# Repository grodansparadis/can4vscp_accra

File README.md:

-----

# The CAN4VSCP Accra general counter module</h1>

This module is part of the [VSCP project](https://www.vscp.org).  It is free to use, modify and sell. The only thing we kindly ask is that improvements and extensions are contributed back to the project (at your will). This to make the project better for everyone. All design files is licensed under the [MIT license](https://en.wikipedia.org/wiki/MIT_License).

The module is documented [here](https://grodansparadis.github.io/can4vscp_accra/#/)

## Abstract

Accra is a general counter module that connects to a CAN4VSCP bus and can count pulses on four channels. The module can be attached to a standard DIN Rail or be mounted directly on a wall.

The module fully adopts to the CAN4VSCP specification and can be powered directly over the bus with a 9-28V DC power source. It has a rich register set for configuration and any information events defined. It also have a decision matrix for easy dynamic event handling.

VSCP CAN modules are designed to work on a VSCP4CAN bus which use ordinary RJ-45 connectors and is powered with 9-30V DC over the same cable. This means there is no need for a separate power cable. All that is needed is a CAT5 or better twisted pair cable. Bus length can be a maximum of 500 meters with drops of maximum 24 meters length (up to a total of 120 meters). As for all VSCP4CAN modules the communication speed is fixed at 125 kbps.

All VSCP modules contains information of there own setup, manual, hardware version, manufacturer etc. You just ask the module for the information you need and you will get it. When they are started up they have a default functionality that often is all that is needed to get a working setup. If the module have something to report it will send you an event and if it is setup to react on a certain type of event it will do it's work when you send event(s) to it. 

---

## Project files

### User manual
  * [User Manual](https://grodansparadis.github.io/can4vscp_accra/#)

### Schematic, PCB, 3D files etc
  * [Schematics reversion A](https://raw.githubusercontent.com/grodansparadis/can4vscp_accra/refs/heads/master/eagle/accra_sch_rev_A.png)
 * Hardware design files is made in [KiCad](https://kicad.org) and can be found in the `kicad` directory. Valid from reversion B of the hardware.
   * Gerber files for PCB production can be found in the `gerber` directory (in the `kicad` folder).
 * Eagle schema and board files for reversion A and B can be found in the `eagle` directory. They are no longer actively updated.

 ### Firmware

 The firmware is developed in [MPLAB X IDE](https://www.microchip.com/mplab/mplab-x-ide) using the [XC8 compiler](https://www.microchip.com/mplab/compilers).

  * Binary release files is available [here](https://github.com/grodansparadis/can4vscp_kelvin_ntc10k/releases)

### MDF - Module Description File(s)
  * [MDF file version: 6 Release date: 2024-04-22](http://www.eurosource.se/accra_1.xml)

### Support
If you need support, please open an issue in the [GitHub repository](https://github.com/grodansparadis/can4vscp_kelvin_ntc10k/issues).

### Buy a ready made modules
You can buy a ready made module from [Grodans Paradis](http://www.grodansparadis.com).

### Project related links
  * [VSCP project](https://www.vscp.org)
  * [VSCP Documentation site](https://docs.vscp.org/)
  * [VSCP Wiki](https://github.com/grodansparadis/vscp/wiki)

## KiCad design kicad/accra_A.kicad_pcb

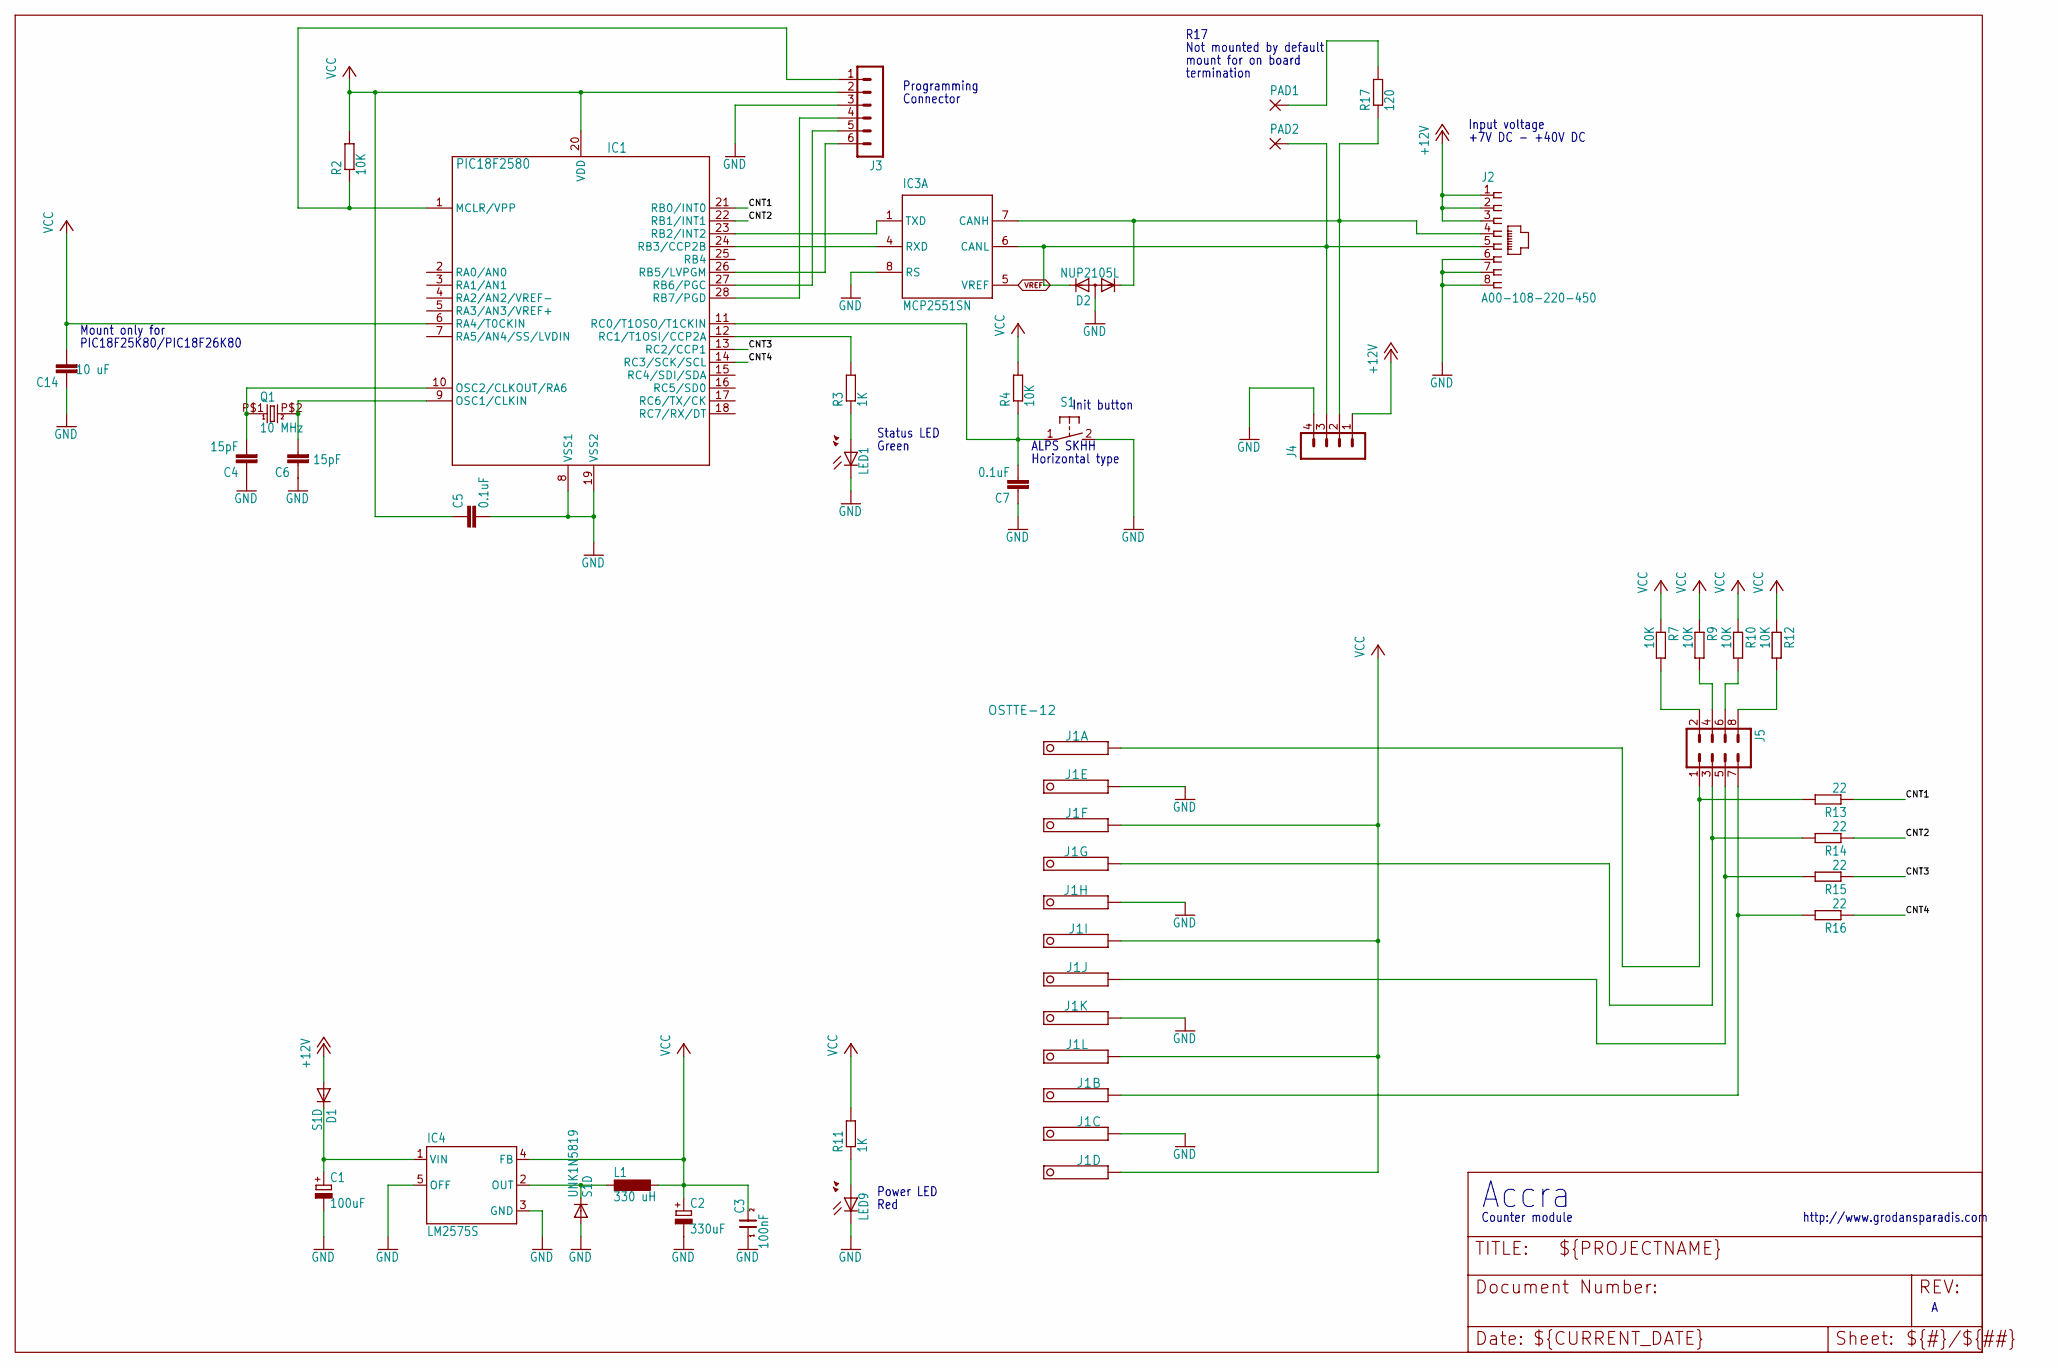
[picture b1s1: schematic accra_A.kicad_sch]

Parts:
C1: 100uF; PANASONIC_D
C2: 330uF; PANASONIC_D
C3: 100nF; 0805
C4, C6: 15pF; C0805
C5, C7: 0.1uF; C0805
C14: 10 uF; C0805
D1: S1D; SOD123
D2: NUP2105L; SOT23
IC1: PIC18F2580; SO28
IC3: MCP2551SN; SO-08
IC4: LM2575S; TO263-5
J1: OSTTE-12; PINHEAD-12
J2: A00-108-220-450; RJ-45
J3: MA06-1
J4: MA04-1
J5: MA04-2
L1: 330 uH; DO3316P
LED1, LED9: LEDCHIP-LED0805; CHIP-LED0805
PAD1, PAD2: 1,6/0,8; 1,6_0,8
Q1: 10 MHz; 9C
R2, R4, R7, R9, R10, R12: 10K; R0805
R3, R11: 1K; R0805
R13, R14, R15, R16: 22; R0805
R17: 120; R0805
S1: 31-XX; B3F-31XX
UNK1N5819: S1D; SOD123

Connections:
+12V: D1.A, J2.1, J2.2, J2.3, J4.1
CANL: D2.2 (K2), IC3.6 (CANL), J2.5, J4.3, PAD2.1
CNT1: IC1.21 (RB0/INT0), R13.1
CNT2: IC1.22 (RB1/INT1), R14.1
CNT3: IC1.13 (RC2/CCP1), R15.1
CNT4: IC1.14 (RC3/SCK/SCL), R16.1
GND: C1.-, C2.-, C3.1, C4.1, C5.2, C6.1, C7.1, C14.1, D2.3 (A), IC1.8 (VSS1), IC1.19 (VSS2), IC3.2 (VSS), IC3.8 (RS), IC4.3 (GND), IC4.5 (OFF), J1.2, J1.5, J1.8, J1.11, J2.6, J2.7, J2.8, J3.3, J4.4, LED1.C, LED9.C, S1.2 (S), UNK1N5819.A
unnamed: IC4.2 (OUT), L1.1, UNK1N5819.C
unnamed: C4.2, IC1.10 (OSC2/CLKOUT/RA6), Q1.P$1 (1)
unnamed: C1.+, D1.C, IC4.1 (VIN)
unnamed: IC1.12 (RC1/T1OSI/CCP2A), R3.2
unnamed: LED1.A, R3.1
unnamed: C7.2, IC1.11 (RC0/T1OSO/T1CKIN), R4.1, S1.1
unnamed: C6.2, IC1.9 (OSC1/CLKIN), Q1.P$2 (2)
unnamed: J1.4, J5.3, R14.2
unnamed: J1.7, J5.5, R15.2
unnamed: PAD1.1, R17.2
unnamed: IC1.1 (MCLR/VPP), J3.1, R2.1
unnamed: IC1.28 (RB7/PGD), J3.4
unnamed: IC1.27 (RB6/PGC), J3.5
unnamed: IC1.26 (RB5/LVPGM), J3.6
unnamed: J1.10, J5.7, R16.2
unnamed: J5.2, R7.2
unnamed: LED9.A, R11.1
unnamed: D2.1 (K1), IC3.7 (CANH), J2.4, J4.2, R17.1
unnamed: J5.4, R9.2
unnamed: J5.6, R10.2
unnamed: J5.8, R12.2
unnamed: J1.1, J5.1, R13.2
RXCAN: IC1.24 (RB3/CCP2B), IC3.4 (RXD)
TXCAN: IC1.23 (RB2/INT2), IC3.1 (TXD)
VCC: C2.+, C3.2, C5.1, C14.2, IC1.6 (RA4/T0CKIN), IC1.20 (VDD), IC3.3 (VDD), IC4.4 (FB), J1.3, J1.6, J1.9, J1.12, J3.2, L1.2, R2.2, R4.2, R7.1, R9.1, R10.1, R11.2, R12.1
VREF: IC3.5 (VREF)

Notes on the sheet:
Connector
PIC18F25K80/PIC18F26K80
Input voltage
Programming
Init button
Power LED
termination
http://www.grodansparadis.com
+7V DC - +40V DC
Red
Status LED
Green
Counter module
Mount only for
mount for on board
ALPS SKHH
Horizontal type
Accra
Not mounted by default
R17

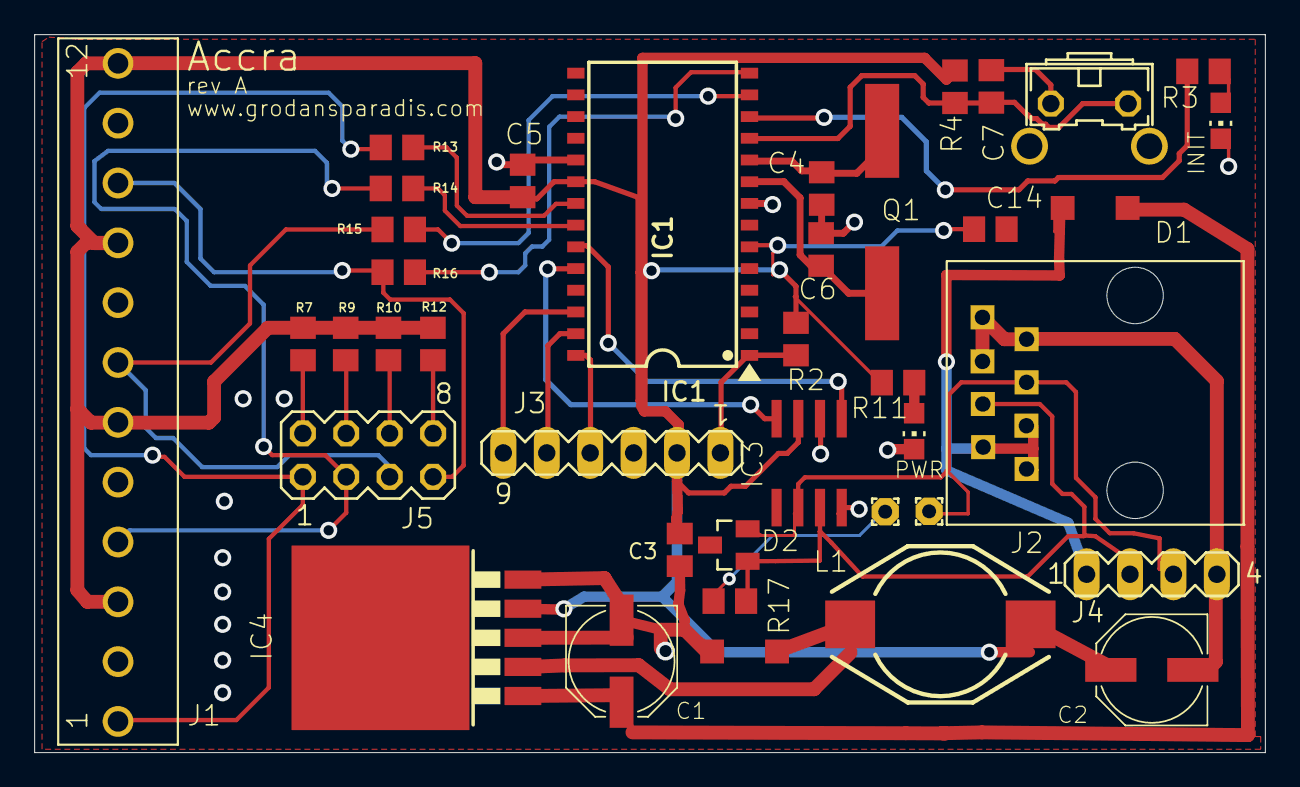
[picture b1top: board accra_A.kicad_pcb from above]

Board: 6 copper layers, 72.0 x 42.0 mm, 39 parts (0 on the bottom side), 32 nets.

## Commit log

2015-06-15 Initial checkin
2015-07-06 Added initial firmware code from beijing
2015-07-08 Compiles but not more
2015-07-27 Fixed problem with send timeout
2015-08-17 Changed license to Artistic License 3.0
2015-08-28 Updated info
2015-11-13 Added firmware read me
2015-11-16 Ground functionality in place
2015-11-17 Register r/w works
2015-11-18 All code in place - Debugfeest
2015-11-20 Changed model to address EEPROM content
2015-11-26 Fixed linear calculation
2015-11-28 Added binary for 1.0.0
2015-11-28 Initial release binaries
2015-12-02 Added images
2015-12-02 Added marker for pin 1
2015-12-07 Edit
2015-12-17 Updated license and readme
2015-12-17 Changed copyright info in headers so it is correct
2016-03-02 Fixed code for new firmware code
2016-03-08 Adopted to 1.6 firmware. Adopted for PIC18F26K80.
2016-03-08 Bumped build version
2016-03-08 Updated copyright info.
2016-03-18 Added some electric meeter design files
2016-03-23 Renamed
2016-03-23 Version 1.0.1
2016-03-23 Version 1.0.2
2016-04-04 Changed value of C14 to 10uF
2016-04-11 vscp_getMatrixInfo nw use the pointer supplied by the framework.
2016-04-19 RA4 set to input to prevent collision with VCAP circuits in PIC18F2580. Brown out raised to maximum (3V & 4.6V). Valable input from Anders Forsgren, AJE Electronics AB.
2016-05-04 Changed bit time calculation link
2016-10-19 Ignored some files
2020-05-08 Increased forced init time. Fixed init bug
2020-05-08 Added firmware
2020-05-08 Updated MDF with firmware pointers
2020-05-08 Added binary files pointers
2020-05-14 Fixed problem with init on power up. Fixed seconds counting.
2020-05-14 Fixed type
2020-05-15 Updated firmware
2020-05-19 Fixed faulty include file
2022-04-22 Updated can module
2022-06-02 Spelling
2022-06-02 Converted docs to Markdown (Docsify)
2022-06-02 Set theme jekyll-theme-cayman
2022-06-02 Set theme jekyll-theme-hacker
2022-06-02 Fixed link thta is wrong
2022-06-02 Added .nojekyll
2022-06-09 Fixed path to schematics
2022-06-09 Added missing file (board layout)
2022-06-09 Added link to documentation
2025-01-13 Updated some links in the documentation
2025-02-07 Formatted history
2025-02-07 Updated info about firmware update of modules
2025-02-07 Removed sidebar logo
2025-02-07 Added links to resources
2025-02-17 Added OSHW images
2025-02-17 Moved order in README
2025-08-18 Converted layout to kicad
2025-09-05 Added links to manual etc
2025-09-05 Updated links to MDF files
2025-09-05 Corrected MDF version
2025-09-05 Old manual retired
2025-09-05 Smaller VSCP logo on cover page
